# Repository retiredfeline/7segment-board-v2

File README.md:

# 7 segment 2 digit board

These are the design files for a 7 segment board similar to [6 segment 2 digit board](https://hackaday.io/project/175397-6-segment-2-digit-led-board).

This is a multiplexed design with 7 cathode segment drive lines plus 1 colon line. The cathode drive lines are taken low to turn on the LEDs, while the anode drive lines are taken low to turn on the transistors.

## Versioning

Release March 2025

## Notes

Most components are installed on the back side and the LEDs are installed on the front side.

The PNP transistors need a gain > 40. A bit more margin is recommended.

Note the the LED supply voltage will need to be higher than 4x the LED drop and the cathode current limiting resistor should be calculated accordingly. So 5V will not be sufficient and also a buffer stage will be needed for most MCUs. For example with a 12V supply and green (not emerald) LEDs, the voltage drop per LED is 2V. The transistor drops will be around 0.8V. That leaves 2.2V to be dropped across the resistor. A 220Ω resistor gives 10mA through the LED. For 4 digits multiplexed this is effectively 2.5mA. Modern LEDs are efficient enough to shine brightly at such currents. For dimming, use PWM.

When cascading only the rightmost board needs to be fully populated. The others need only the LEDs, the anode driver transistors, and its resistors. The cathode resistors are not installed and the solder jumpers are closed.

## Authors

* **Ken Yap**

## License

See the [LICENSE](LICENSE.md) file for license rights and limitations (MIT).

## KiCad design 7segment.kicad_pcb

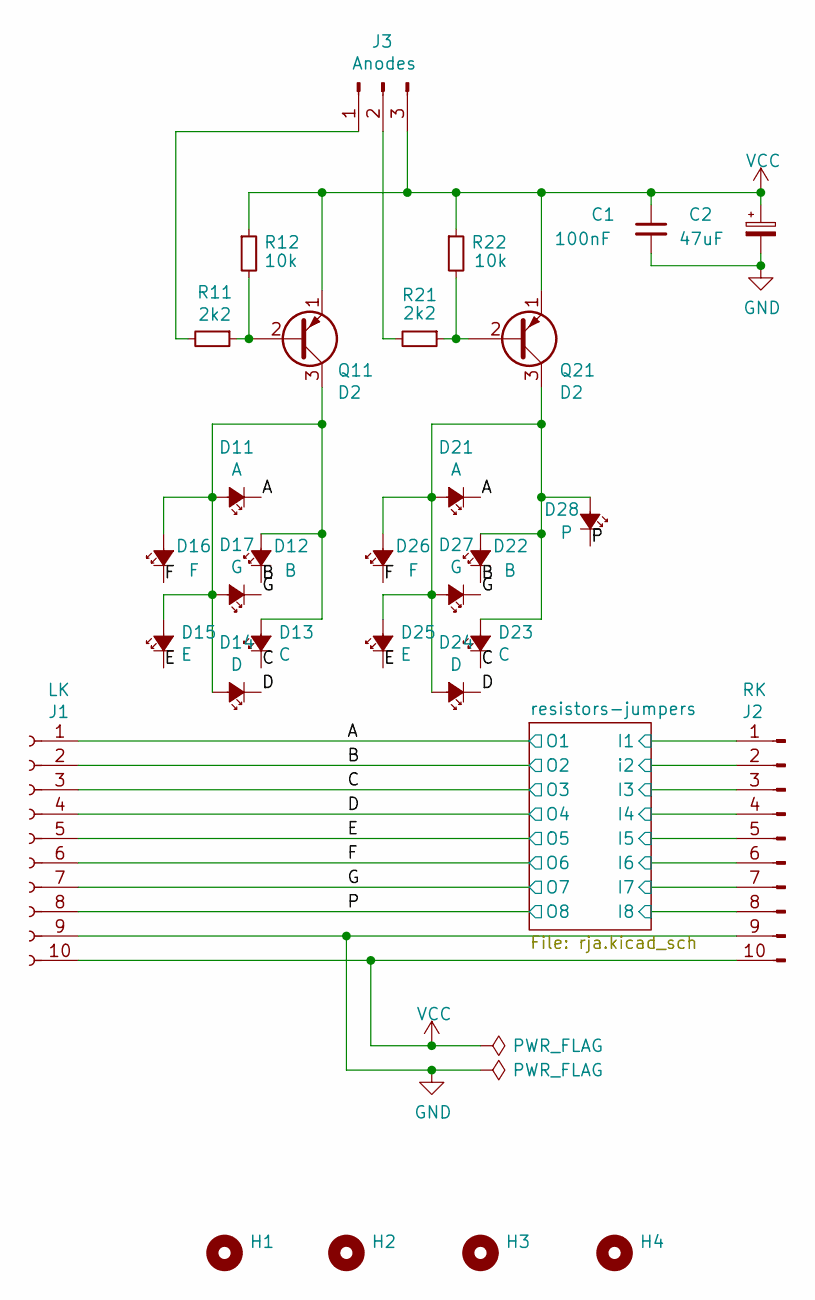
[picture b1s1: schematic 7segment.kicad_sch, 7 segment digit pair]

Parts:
C1: 100nF; C_Disc_D3.8mm_W2.6mm_P2.50mm
C2: 47uF; CP_Radial_D5.0mm_P2.50mm
D11, D21: A; LED_D3.0mmx4
D12, D22: B; LED_D3.0mmx4
D13, D23: C; LED_D3.0mmx4
D14, D24: D; LED_D3.0mmx4
D15, D25: E; LED_D3.0mmx4
D16, D26: F; LED_D3.0mmx4
D17, D27: G; LED_D3.0mmx4
D28: P; LED_D3.0mm-colon
H1, H2, H3, H4: MountingHole; MountingHole_3.5mm
J1: LK; PinSocket_1x10_P2.54mm_Vertical
J2: RK; PinHeader_1x10_P2.54mm_Vertical
J3: Anodes; PinHeader_1x03_P2.54mm_Vertical
Q11, Q21: D2; TO-92_Wide
R11, R21: 2k2; R_Axial_DIN0207_L6.3mm_D2.5mm_P10.16mm_Horizontal
R12, R22: 10k; R_Axial_DIN0207_L6.3mm_D2.5mm_P10.16mm_Horizontal

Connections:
/A: D11.1 (K), D21.1 (K), J1.1; also elsewhere on the board
/B: D12.1 (K), D22.1 (K), J1.2; also elsewhere on the board
/C: D13.1 (K), D23.1 (K), J1.3; also elsewhere on the board
/D: D14.1 (K), D24.1 (K), J1.4; also elsewhere on the board
/E: D15.1 (K), D25.1 (K), J1.5; also elsewhere on the board
/F: D16.1 (K), D26.1 (K), J1.6; also elsewhere on the board
/G: D17.1 (K), D27.1 (K), J1.7; also elsewhere on the board
/P: D28.1 (K), J1.8; also elsewhere on the board
/resistors-jumpers/I1: J2.1; also elsewhere on the board
/resistors-jumpers/I3: J2.3; also elsewhere on the board
/resistors-jumpers/I4: J2.4; also elsewhere on the board
/resistors-jumpers/I5: J2.5; also elsewhere on the board
/resistors-jumpers/I6: J2.6; also elsewhere on the board
/resistors-jumpers/I7: J2.7; also elsewhere on the board
/resistors-jumpers/I8: J2.8; also elsewhere on the board
/resistors-jumpers/i2: J2.2; also elsewhere on the board
GND: C1.2, C2.2, J1.9, J2.9
unnamed: D11.2 (A), D12.2 (A), D13.2 (A), D14.2 (A), D15.2 (A), D16.2 (A), D17.2 (A), Q11.3 (C)
unnamed: D21.2 (A), D22.2 (A), D23.2 (A), D24.2 (A), D25.2 (A), D26.2 (A), D27.2 (A), D28.2 (A), Q21.3 (C)
unnamed: J3.1, R11.2
unnamed: J3.2, R21.2
unnamed: Q11.2 (B), R11.1, R12.2
unnamed: Q21.2 (B), R21.1, R22.2
VCC: C1.1, C2.1, J1.10, J2.10, J3.3, Q11.1 (E), Q21.1 (E), R12.1, R22.1

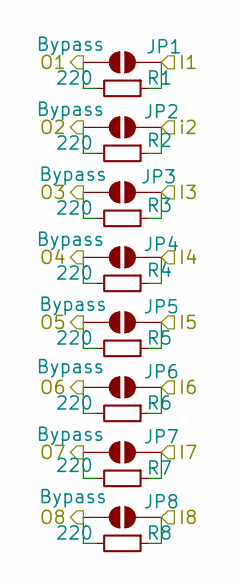
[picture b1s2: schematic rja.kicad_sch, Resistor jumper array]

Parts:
JP1, JP2, JP3, JP4, JP5, JP6, JP7, JP8: Bypass; SolderJumper-2_P1.3mm_Open_TrianglePad1.0x1.5mm
R1, R2, R3, R4, R5, R6, R7, R8: 220; R_Axial_DIN0207_L6.3mm_D2.5mm_P10.16mm_Horizontal

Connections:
/A: JP1.2 (B), R1.2; also elsewhere on the board
/B: JP2.2 (B), R2.2; also elsewhere on the board
/C: JP3.2 (B), R3.2; also elsewhere on the board
/D: JP4.2 (B), R4.2; also elsewhere on the board
/E: JP5.2 (B), R5.2; also elsewhere on the board
/F: JP6.2 (B), R6.2; also elsewhere on the board
/G: JP7.2 (B), R7.2; also elsewhere on the board
/P: JP8.2 (B), R8.2; also elsewhere on the board
/resistors-jumpers/I1: JP1.1 (A), R1.1; also elsewhere on the board
/resistors-jumpers/I3: JP3.1 (A), R3.1; also elsewhere on the board
/resistors-jumpers/I4: JP4.1 (A), R4.1; also elsewhere on the board
/resistors-jumpers/I5: JP5.1 (A), R5.1; also elsewhere on the board
/resistors-jumpers/I6: JP6.1 (A), R6.1; also elsewhere on the board
/resistors-jumpers/I7: JP7.1 (A), R7.1; also elsewhere on the board
/resistors-jumpers/I8: JP8.1 (A), R8.1; also elsewhere on the board
/resistors-jumpers/i2: JP2.1 (A), R2.1; also elsewhere on the board

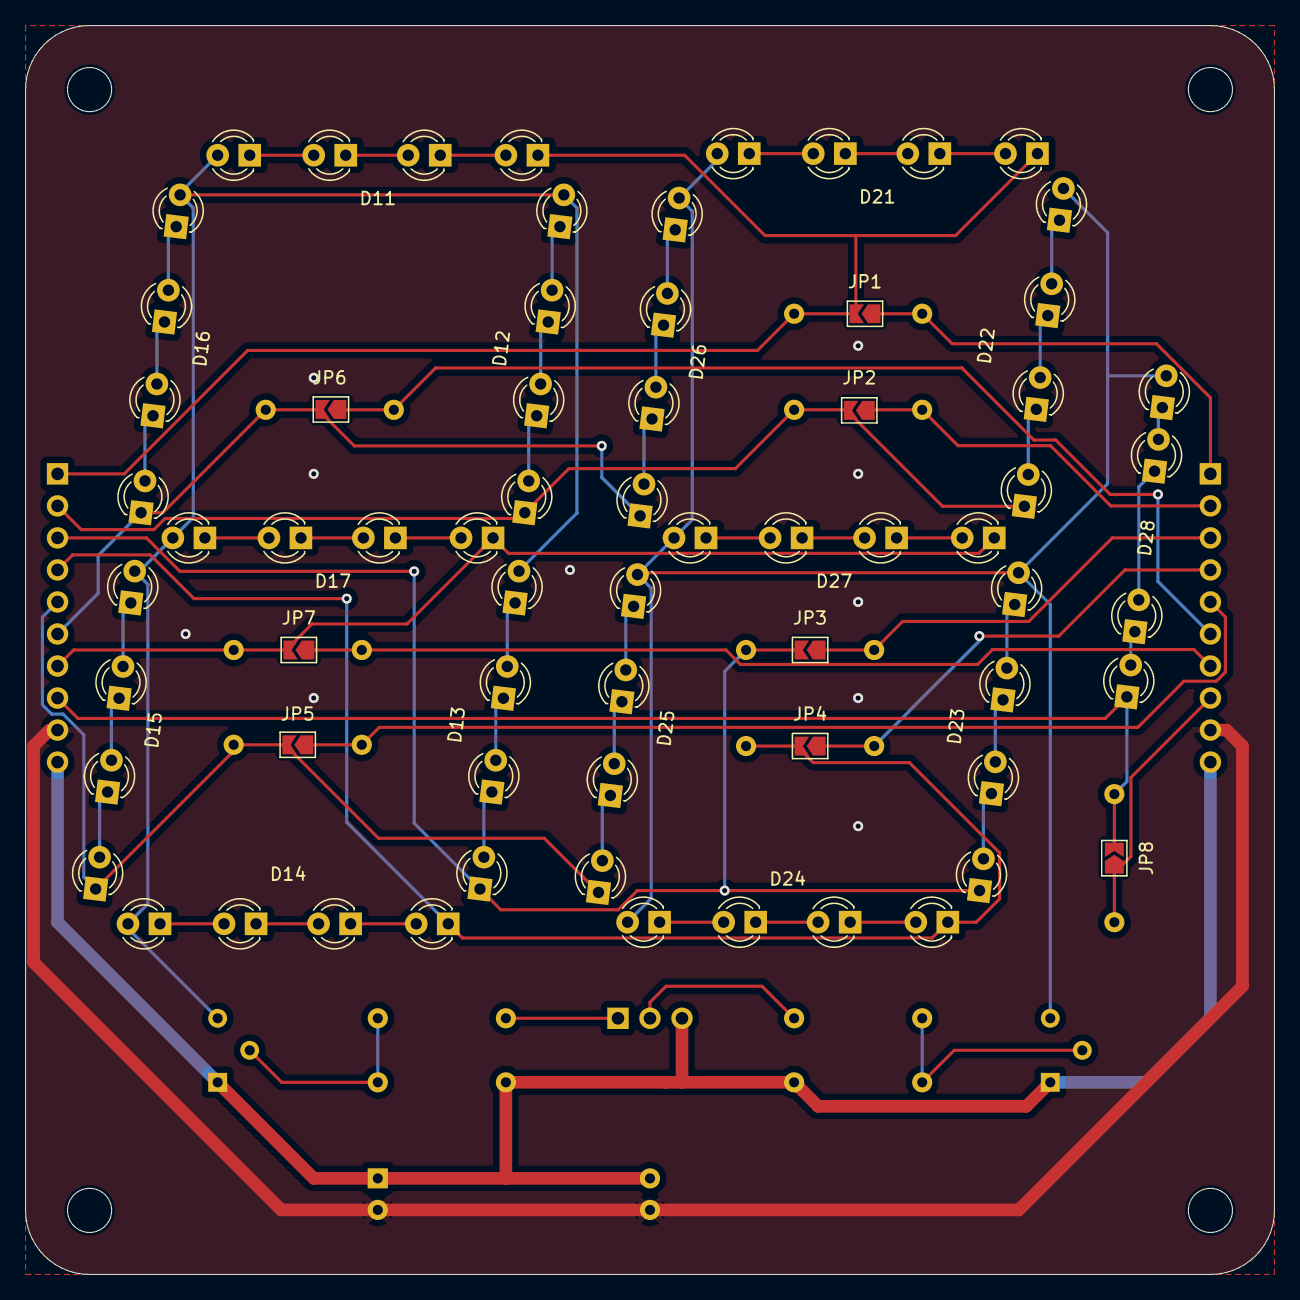
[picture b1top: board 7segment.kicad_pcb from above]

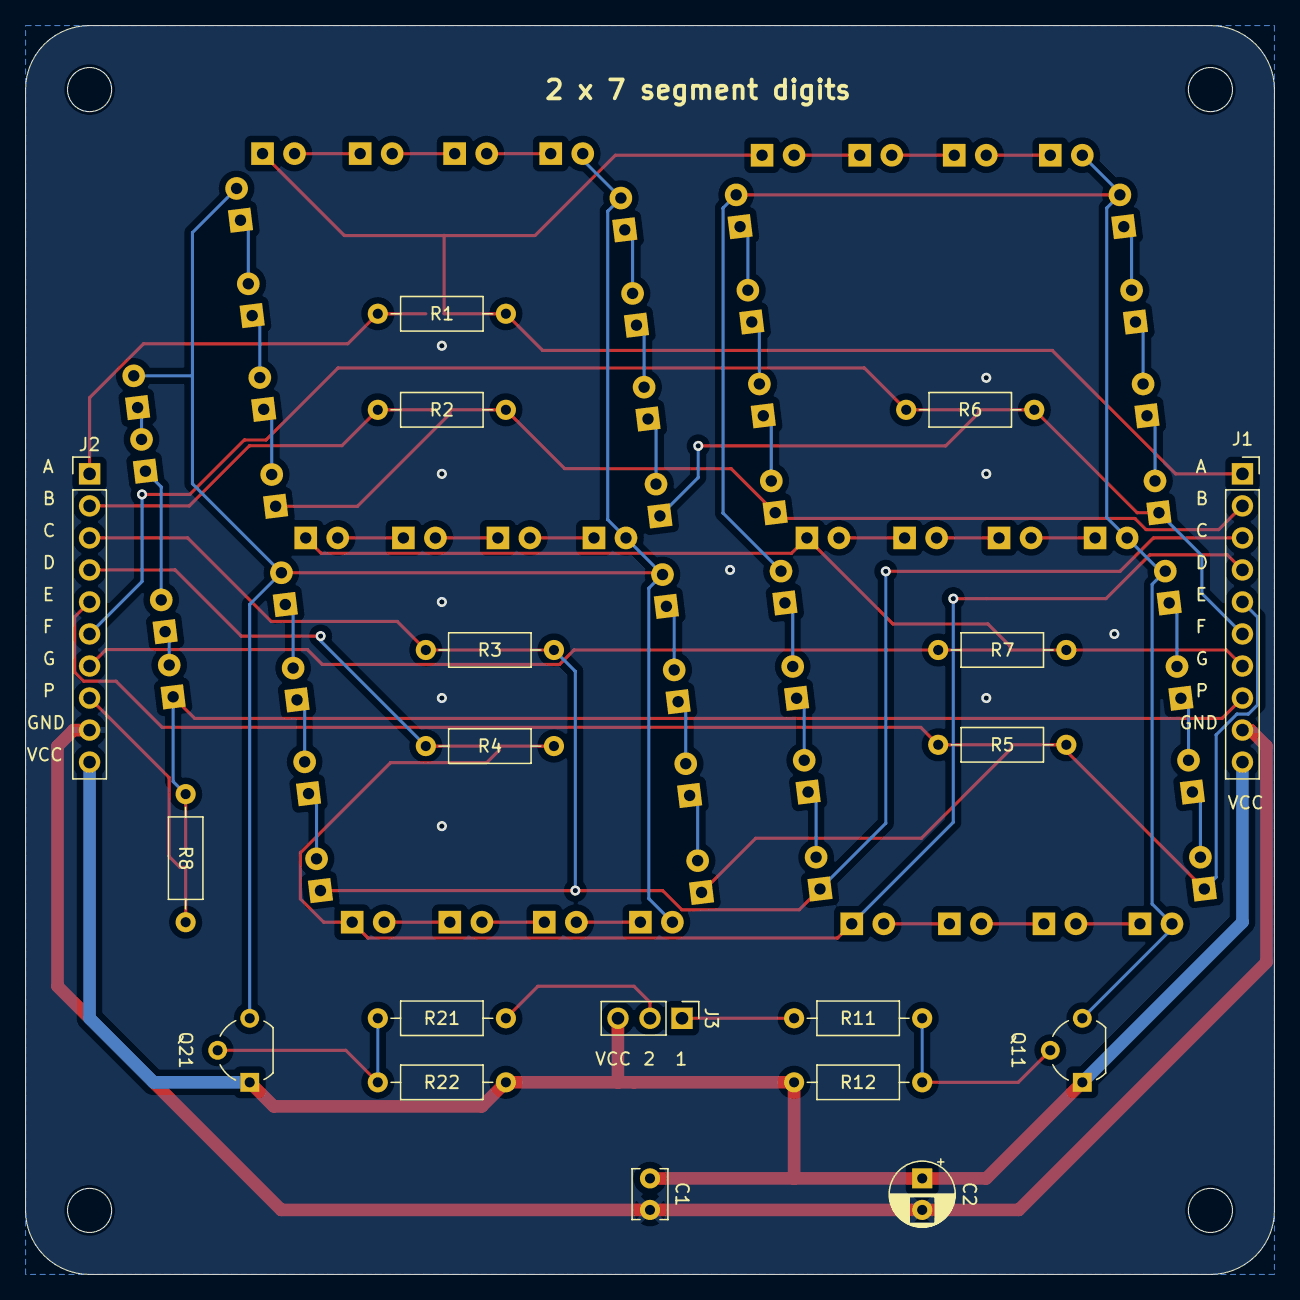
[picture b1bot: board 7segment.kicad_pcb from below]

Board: 2 copper layers, 99.1 x 99.1 mm, 46 parts (19 on the bottom side), 24 nets.

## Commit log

2025-03-11 Initial checkin
2025-04-16 Use copyright symbol
